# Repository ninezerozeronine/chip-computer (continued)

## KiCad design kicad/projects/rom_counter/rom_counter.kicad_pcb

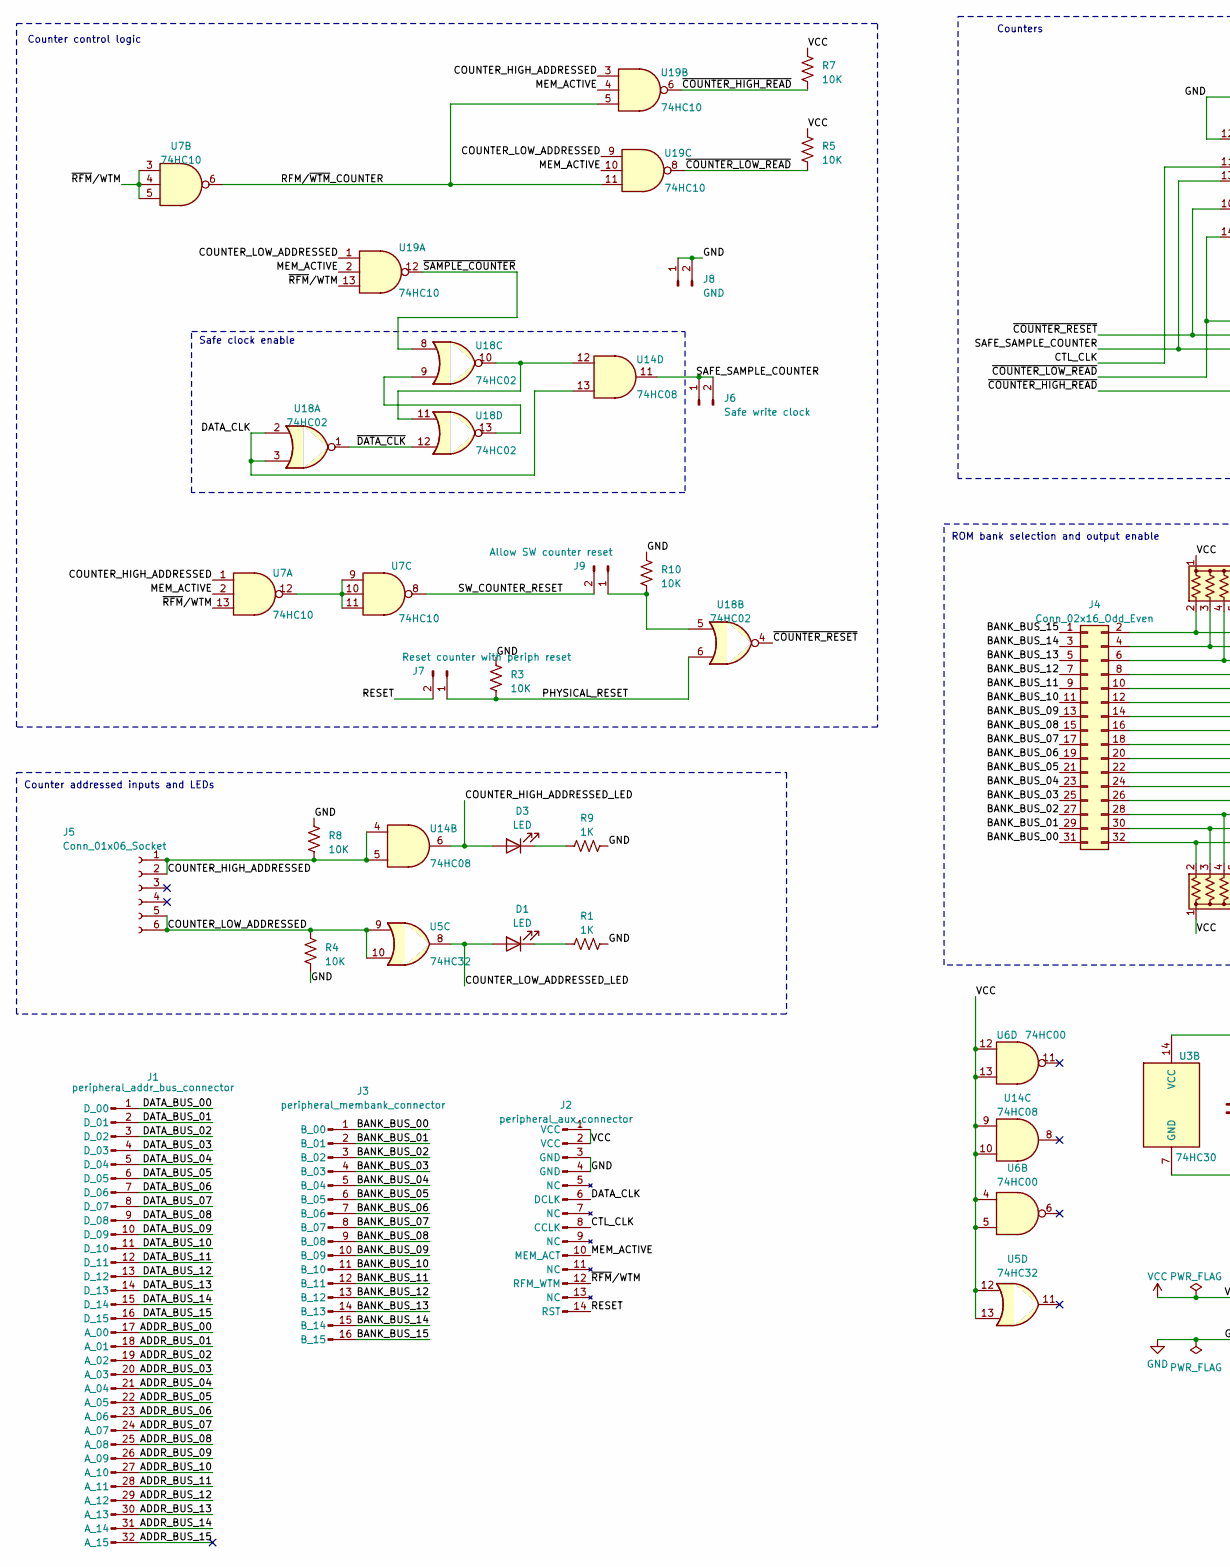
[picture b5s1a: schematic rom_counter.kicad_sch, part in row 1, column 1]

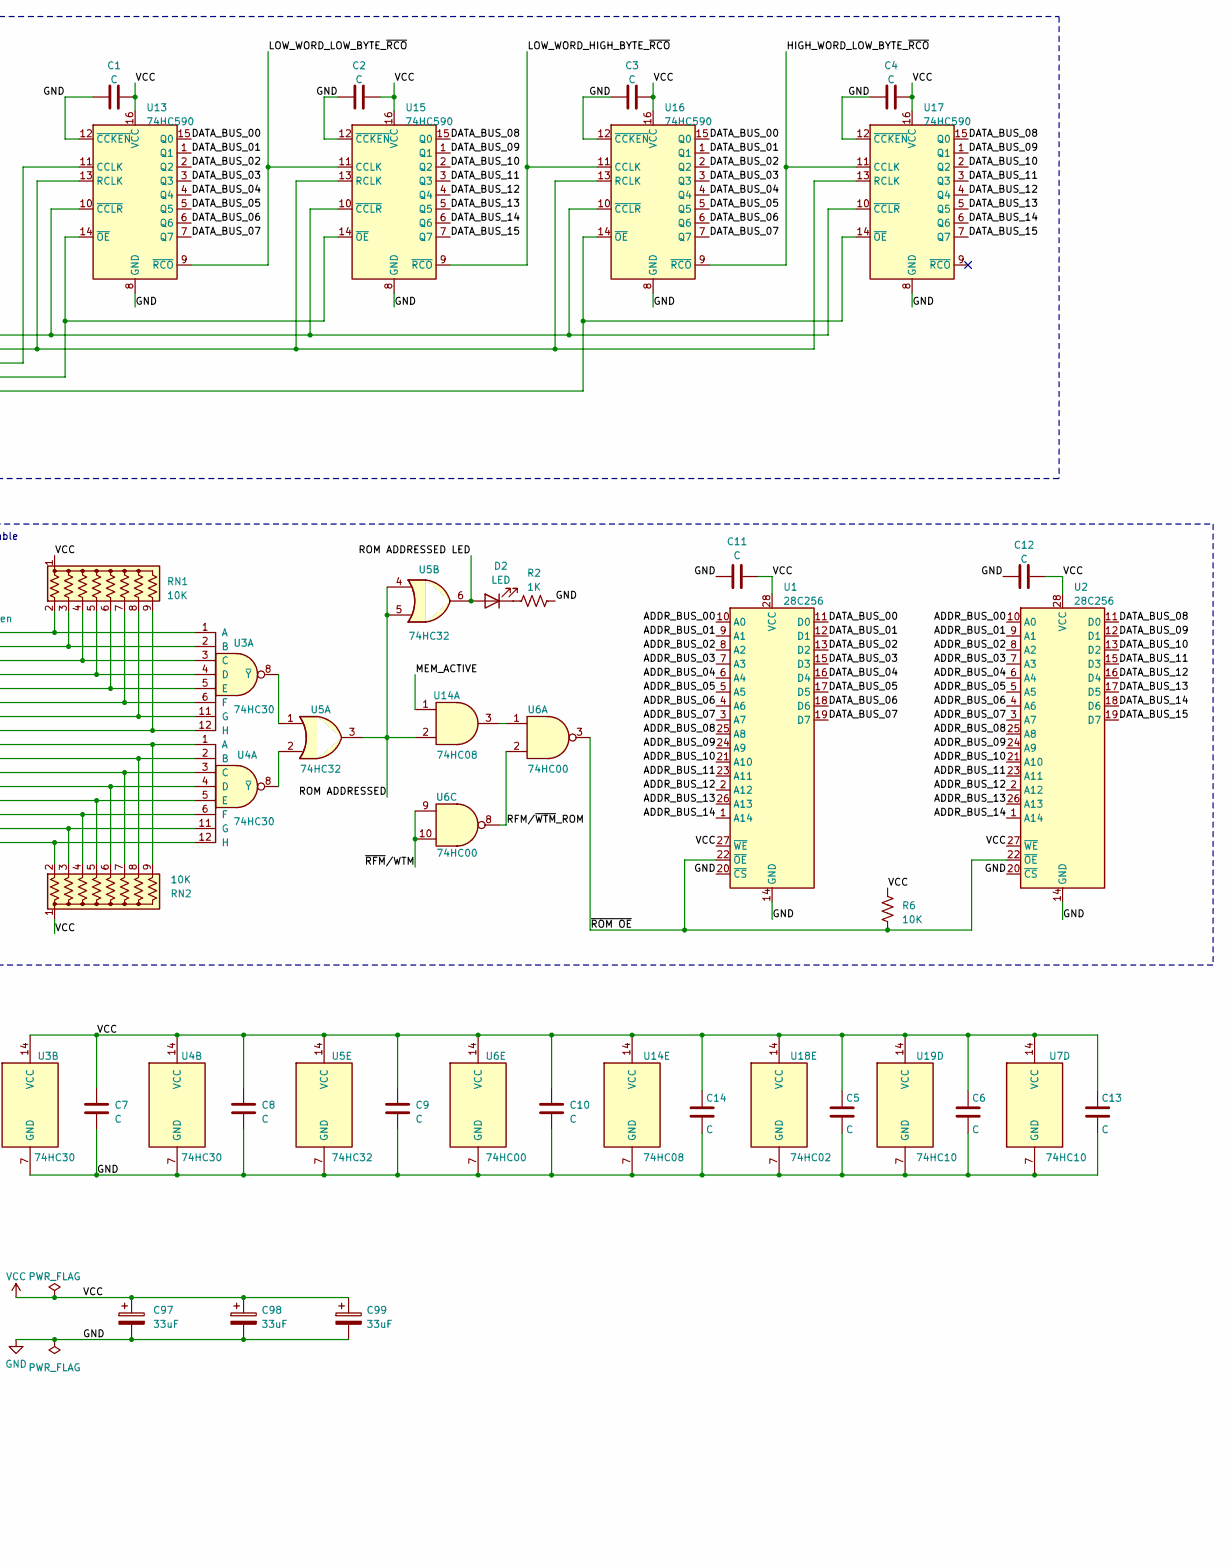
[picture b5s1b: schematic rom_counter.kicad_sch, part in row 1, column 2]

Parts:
C1, C2, C3, C4, C5, C6, C7, C8, C9, C10, C11, C12, C13, C14: C; C_Disc_D5.0mm_W2.5mm_P5.00mm
C97, C98, C99: 33uF; CP_Radial_D6.3mm_P2.50mm
D1, D2, D3: LED; LED_D5.0mm_Horizontal_O3.81mm_Z3.0mm
J1: peripheral_addr_bus_connector; peripheral-backplane-data-addr-anno
J2: peripheral_aux_connector; peripheral-backplane-aux
J3: peripheral_membank_connector; peripheral-backplane-membank
J4: Conn_02x16_Odd_Even; PinHeader_2x16_P2.54mm_Vertical
J5: Conn_01x06_Socket; PinSocket_1x06_P2.54mm_Horizontal
J6: Safe write clock; PinHeader_1x02_P2.54mm_Vertical
J7: Reset counter with periph reset; PinHeader_1x02_P2.54mm_Horizontal
J8: GND; PinHeader_1x02_P2.54mm_Vertical
J9: Allow SW counter reset; PinHeader_1x02_P2.54mm_Horizontal
R1, R2, R9: 1K; R_Axial_DIN0207_L6.3mm_D2.5mm_P10.16mm_Horizontal
R3, R4, R5, R6, R7, R8, R10: 10K; R_Axial_DIN0207_L6.3mm_D2.5mm_P10.16mm_Horizontal
RN1, RN2: 10K; R_Array_SIP9
U1, U2: 28C256; DIP-28_W15.24mm_Socket
U3, U4: 74HC30; DIP-14_W7.62mm_Socket
U5: 74HC32; DIP-14_W7.62mm_Socket
U6: 74HC00; DIP-14_W7.62mm_Socket
U7, U19: 74HC10; DIP-14_W7.62mm_Socket
U13, U15, U16, U17: 74HC590; DIP-16_W7.62mm_Socket
U14: 74HC08; DIP-14_W7.62mm_Socket
U18: 74HC02; DIP-14_W7.62mm_Socket

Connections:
/ADDR_BUS_00: J1.17 (A_00), U1.10 (A0), U2.10 (A0)
/ADDR_BUS_01: J1.18 (A_01), U1.9 (A1), U2.9 (A1)
/ADDR_BUS_02: J1.19 (A_02), U1.8 (A2), U2.8 (A2)
/ADDR_BUS_03: J1.20 (A_03), U1.7 (A3), U2.7 (A3)
/ADDR_BUS_04: J1.21 (A_04), U1.6 (A4), U2.6 (A4)
/ADDR_BUS_05: J1.22 (A_05), U1.5 (A5), U2.5 (A5)
/ADDR_BUS_06: J1.23 (A_06), U1.4 (A6), U2.4 (A6)
/ADDR_BUS_07: J1.24 (A_07), U1.3 (A7), U2.3 (A7)
/ADDR_BUS_08: J1.25 (A_08), U1.25 (A8), U2.25 (A8)
/ADDR_BUS_09: J1.26 (A_09), U1.24 (A9), U2.24 (A9)
/ADDR_BUS_10: J1.27 (A_10), U1.21 (A10), U2.21 (A10)
/ADDR_BUS_11: J1.28 (A_11), U1.23 (A11), U2.23 (A11)
/ADDR_BUS_12: J1.29 (A_12), U1.2 (A12), U2.2 (A12)
/ADDR_BUS_13: J1.30 (A_13), U1.26 (A13), U2.26 (A13)
/ADDR_BUS_14: J1.31 (A_14), U1.1 (A14), U2.1 (A14)
/ADDR_BUS_15: J1.32 (A_15)
/BANK_BUS_00: J3.1 (B_00), J4.31
/BANK_BUS_01: J3.2 (B_01), J4.29
/BANK_BUS_02: J3.3 (B_02), J4.27
/BANK_BUS_03: J3.4 (B_03), J4.25
/BANK_BUS_04: J3.5 (B_04), J4.23
/BANK_BUS_05: J3.6 (B_05), J4.21
/BANK_BUS_06: J3.7 (B_06), J4.19
/BANK_BUS_07: J3.8 (B_07), J4.17
/BANK_BUS_08: J3.9 (B_08), J4.15
/BANK_BUS_09: J3.10 (B_09), J4.13
/BANK_BUS_10: J3.11 (B_10), J4.11
/BANK_BUS_11: J3.12 (B_11), J4.9
/BANK_BUS_12: J3.13 (B_12), J4.7
/BANK_BUS_13: J3.14 (B_13), J4.5
/BANK_BUS_14: J3.15 (B_14), J4.3
/BANK_BUS_15: J3.16 (B_15), J4.1
/COUNTER_HIGH_ADDRESSED: J5.1, J5.2, R8.1, U7.1, U14.4, U14.5, U19.3
/COUNTER_HIGH_ADDRESSED_LED: D3.2 (A), U14.6
/COUNTER_LOW_ADDRESSED: J5.5, J5.6, R4.2, U5.9, U5.10, U19.1, U19.9
/COUNTER_LOW_ADDRESSED_LED: D1.2 (A), U5.8
/CTL_CLK: J2.8 (CCLK), U13.11 (CCLK)
/DATA_BUS_00: J1.1 (D_00), U1.11 (D0), U13.15 (Q0), U16.15 (Q0)
/DATA_BUS_01: J1.2 (D_01), U1.12 (D1), U13.1 (Q1), U16.1 (Q1)
/DATA_BUS_02: J1.3 (D_02), U1.13 (D2), U13.2 (Q2), U16.2 (Q2)
/DATA_BUS_03: J1.4 (D_03), U1.15 (D3), U13.3 (Q3), U16.3 (Q3)
/DATA_BUS_04: J1.5 (D_04), U1.16 (D4), U13.4 (Q4), U16.4 (Q4)
/DATA_BUS_05: J1.6 (D_05), U1.17 (D5), U13.5 (Q5), U16.5 (Q5)
/DATA_BUS_06: J1.7 (D_06), U1.18 (D6), U13.6 (Q6), U16.6 (Q6)
/DATA_BUS_07: J1.8 (D_07), U1.19 (D7), U13.7 (Q7), U16.7 (Q7)
/DATA_BUS_08: J1.9 (D_08), U2.11 (D0), U15.15 (Q0), U17.15 (Q0)
/DATA_BUS_09: J1.10 (D_09), U2.12 (D1), U15.1 (Q1), U17.1 (Q1)
/DATA_BUS_10: J1.11 (D_10), U2.13 (D2), U15.2 (Q2), U17.2 (Q2)
/DATA_BUS_11: J1.12 (D_11), U2.15 (D3), U15.3 (Q3), U17.3 (Q3)
/DATA_BUS_12: J1.13 (D_12), U2.16 (D4), U15.4 (Q4), U17.4 (Q4)
/DATA_BUS_13: J1.14 (D_13), U2.17 (D5), U15.5 (Q5), U17.5 (Q5)
/DATA_BUS_14: J1.15 (D_14), U2.18 (D6), U15.6 (Q6), U17.6 (Q6)
/DATA_BUS_15: J1.16 (D_15), U2.19 (D7), U15.7 (Q7), U17.7 (Q7)
/DATA_CLK: J2.6 (DCLK), U14.13, U18.2, U18.3
/HIGH_WORD_LOW_BYTE_~RCO: U16.9 (~RCO), U17.11 (CCLK)
/LOW_WORD_HIGH_BYTE_~RCO: U15.9 (~RCO), U16.11 (CCLK)
/LOW_WORD_LOW_BYTE_~RCO: U13.9 (~RCO), U15.11 (CCLK)
/MEM_ACTIVE: J2.10 (MEM_ACT), U7.2, U14.1, U19.2, U19.4, U19.10
/PHYSICAL_RESET: J7.1, R3.1, U18.6
/RESET: J2.14 (RST), J7.2
/RFM/~WTM_COUNTER: U7.6, U19.5, U19.11
/RFM/~WTM_ROM: U6.2, U6.8
/ROM ADDRESSED: U5.3, U5.4, U5.5, U14.2
/ROM ADDRESSED LED: D2.2 (A), U5.6
/SAFE_SAMPLE_COUNTER: J6.1, J6.2, U13.13 (RCLK), U14.11, U15.13 (RCLK), U16.13 (RCLK), U17.13 (RCLK)
/SW_COUNTER_RESET: J9.2, U7.8
/~COUNTER_HIGH_READ: R7.1, U16.14 (~OE), U17.14 (~OE), U19.6
/~COUNTER_LOW_READ: R5.1, U13.14 (~OE), U15.14 (~OE), U19.8
/~COUNTER_RESET: U13.10 (~CCLR), U15.10 (~CCLR), U16.10 (~CCLR), U17.10 (~CCLR), U18.4
/~DATA_CLK: U18.1, U18.12
/~RFM/WTM: J2.12 (RFM_WTM), U6.9, U6.10, U7.3, U7.4, U7.5, U7.13, U19.13
/~ROM OE: R6.2, U1.22 (~OE), U2.22 (~OE), U6.3
/~SAMPLE_COUNTER: U18.8, U19.12
GND: C1.1, C2.1, C3.1, C4.1, C5.1, C6.1, C7.1, C8.1, C9.1, C10.1, C11.2, C12.2, C13.1, C14.1, C97.2, C98.2, C99.2, J2.3 (GND), J2.4 (GND), J8.1, J8.2, R1.2, R2.2, R3.2, R4.1, R8.2, R9.2, R10.1, U1.14 (GND), U1.20 (~CS), U2.14 (GND), U2.20 (~CS), U3.7 (GND), U4.7 (GND), U5.7 (GND), U6.7 (GND), U7.7 (GND), U13.8 (GND), U13.12 (~CCKEN), U14.7 (GND), U15.8 (GND), U15.12 (~CCKEN), U16.8 (GND), U16.12 (~CCKEN), U17.8 (GND), U17.12 (~CCKEN), U18.7 (GND), U19.7 (GND)
unnamed: D1.1 (K), R1.1
unnamed: D2.1 (K), R2.1
unnamed: D3.1 (K), R9.1
unnamed: J4.2, RN1.2 (R1), U3.1 (A)
unnamed: J4.4, RN1.3 (R2), U3.2 (B)
unnamed: J4.6, RN1.4 (R3), U3.3 (C)
unnamed: J4.8, RN1.5 (R4), U3.4 (D)
unnamed: J4.10, RN1.6 (R5), U3.5 (E)
unnamed: J4.12, RN1.7 (R6), U3.6 (F)
unnamed: J4.14, RN1.8 (R7), U3.11 (G)
unnamed: J4.16, RN1.9 (R8), U3.12 (H)
unnamed: J4.18, RN2.9 (R8), U4.1 (A)
unnamed: J4.20, RN2.8 (R7), U4.2 (B)
unnamed: J4.22, RN2.7 (R6), U4.3 (C)
unnamed: J4.24, RN2.6 (R5), U4.4 (D)
unnamed: J4.26, RN2.5 (R4), U4.5 (E)
unnamed: J4.28, RN2.4 (R3), U4.6 (F)
unnamed: J4.30, RN2.3 (R2), U4.11 (G)
unnamed: J4.32, RN2.2 (R1), U4.12 (H)
unnamed: J9.1, R10.2, U18.5
unnamed: U3.8 (~Y), U5.1
unnamed: U4.8 (~Y), U5.2
unnamed: U7.9, U7.10, U7.11, U7.12
unnamed: U6.1, U14.3
unnamed: U14.12, U18.10, U18.11
unnamed: U18.9, U18.13
VCC: C1.2, C2.2, C3.2, C4.2, C5.2, C6.2, C7.2, C8.2, C9.2, C10.2, C11.1, C12.1, C13.2, C14.2, C97.1, C98.1, C99.1, J2.1 (VCC), J2.2 (VCC), R5.2, R6.1, R7.2, RN1.1 (common), RN2.1 (common), U1.27 (~WE), U1.28 (VCC), U2.27 (~WE), U2.28 (VCC), U3.14 (VCC), U4.14 (VCC), U5.12, U5.13, U5.14 (VCC), U6.4, U6.5, U6.12, U6.13, U6.14 (VCC), U7.14 (VCC), U13.16 (VCC), U14.9, U14.10, U14.14 (VCC), U15.16 (VCC), U16.16 (VCC), U17.16 (VCC), U18.14 (VCC), U19.14 (VCC)

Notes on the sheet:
Safe clock enable
ROM bank selection and output enable
Counters
Counter addressed inputs and LEDs
Counter control logic

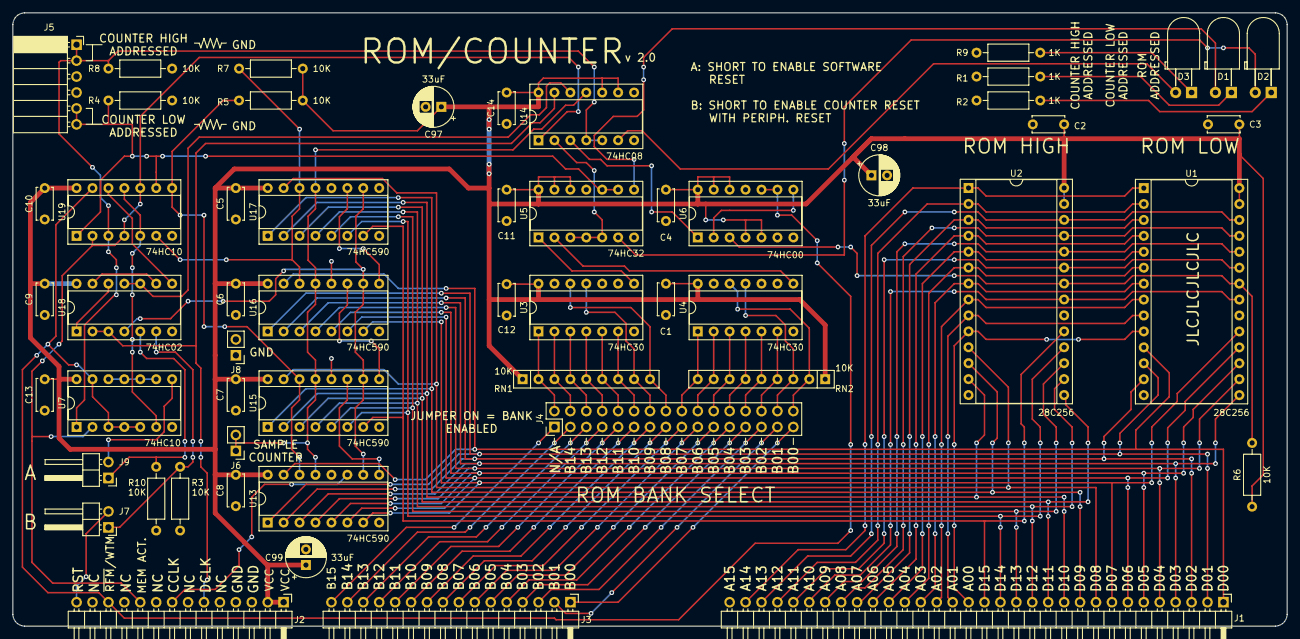
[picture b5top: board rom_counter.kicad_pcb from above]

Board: 2 copper layers, 203.2 x 97.8 mm, 55 parts (0 on the bottom side), 100 nets.

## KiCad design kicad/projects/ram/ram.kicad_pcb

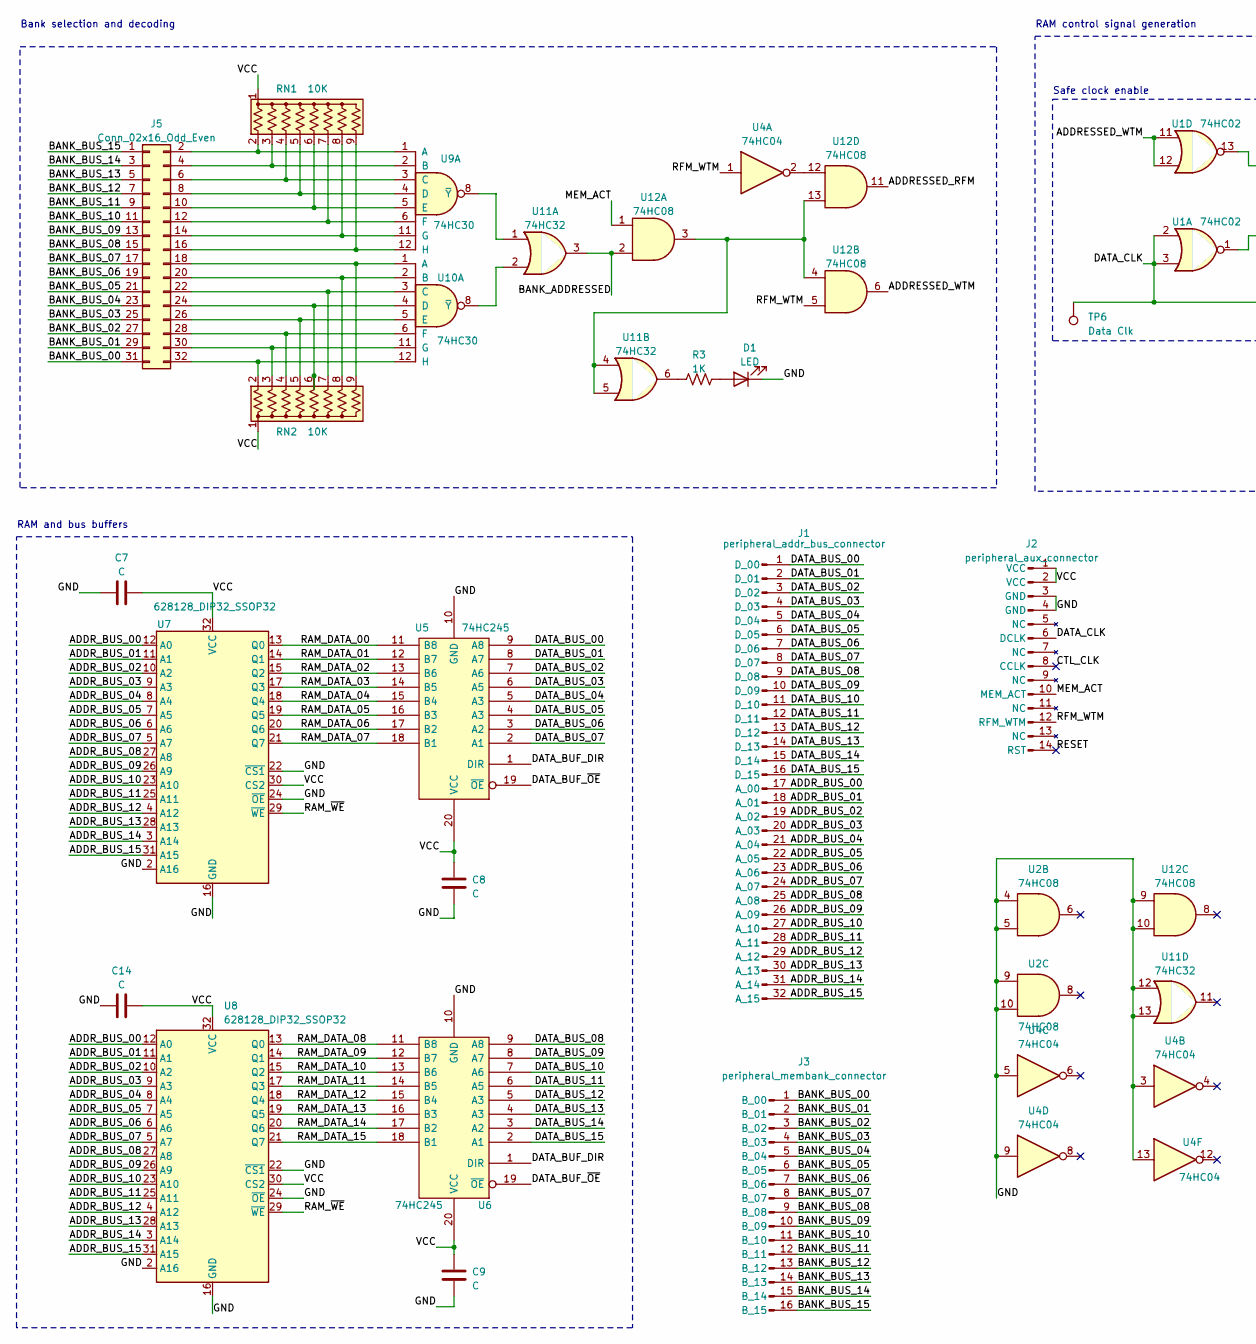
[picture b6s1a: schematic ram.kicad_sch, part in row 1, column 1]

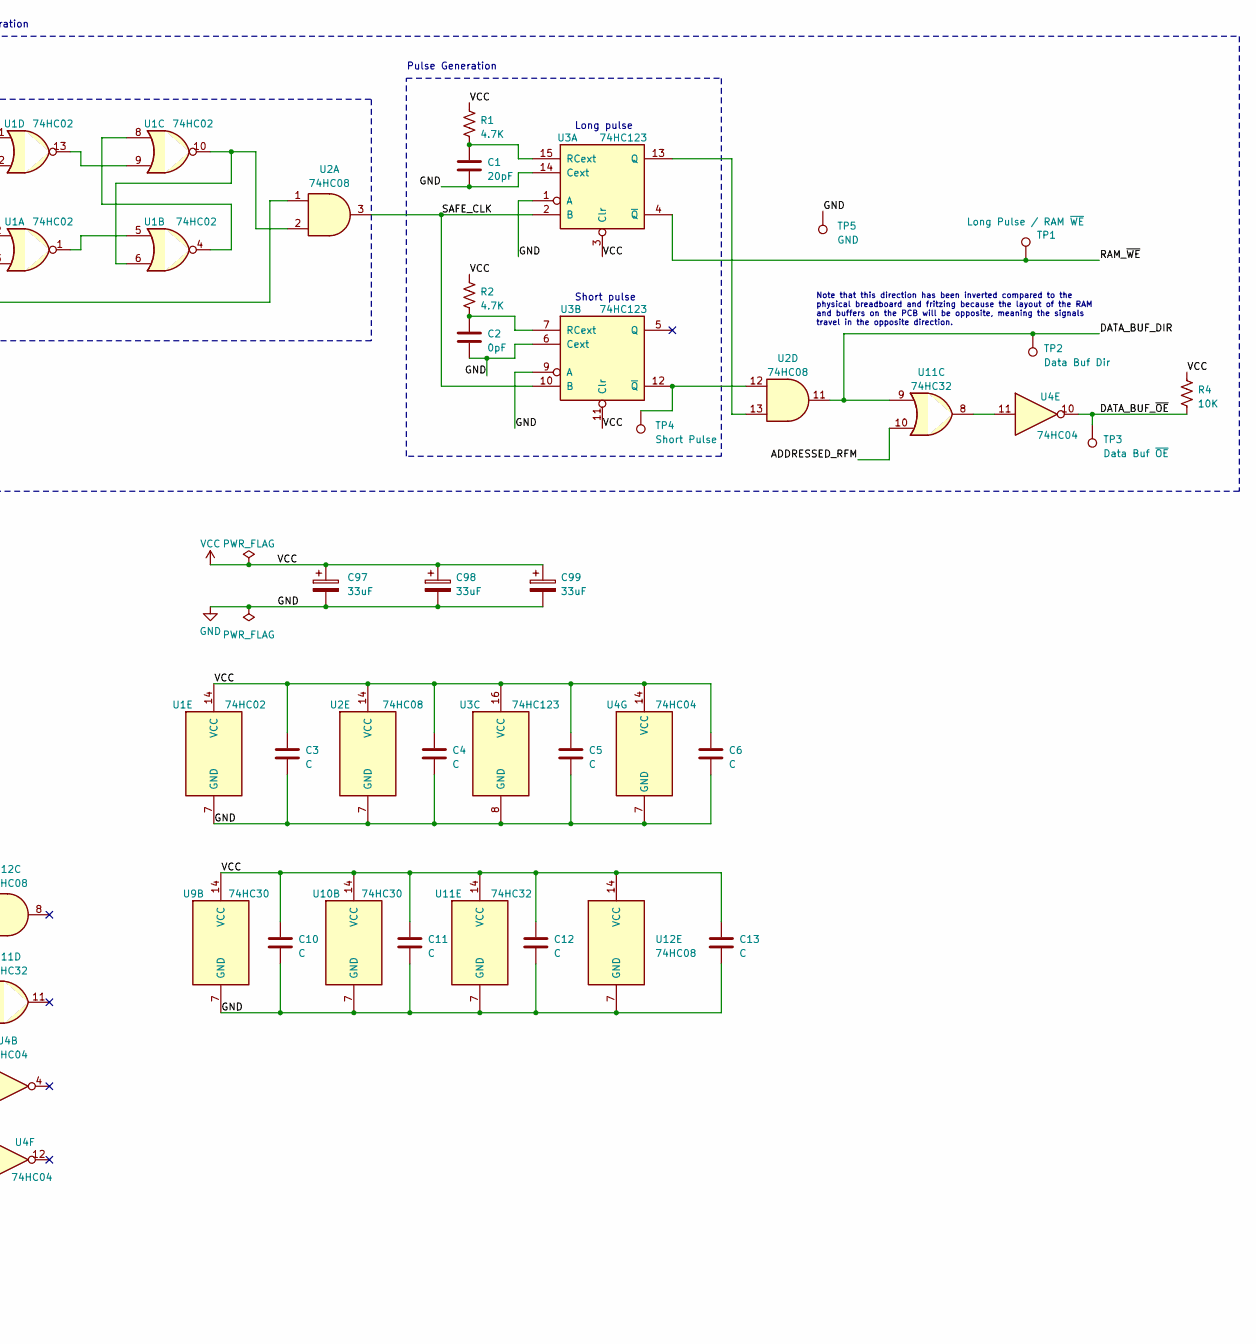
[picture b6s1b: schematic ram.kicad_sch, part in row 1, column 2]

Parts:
C1: 20pF; C_Disc_D5.0mm_W2.5mm_P5.00mm
C2: 0pF; C_Disc_D5.0mm_W2.5mm_P5.00mm
C3, C4, C5, C6, C7, C8, C9, C10, C11, C12, C13, C14: C; C_Disc_D5.0mm_W2.5mm_P5.00mm
C97, C98, C99: 33uF; CP_Radial_D6.3mm_P2.50mm
D1: LED; LED_D5.0mm_Horizontal_O3.81mm_Z3.0mm
J1: peripheral_addr_bus_connector; peripheral-backplane-data-addr-anno
J2: peripheral_aux_connector; peripheral-backplane-aux
J3: peripheral_membank_connector; peripheral-backplane-membank
J5: Conn_02x16_Odd_Even; PinHeader_2x16_P2.54mm_Vertical
R1, R2: 4.7K; R_Axial_DIN0207_L6.3mm_D2.5mm_P10.16mm_Horizontal
R3: 1K; R_Axial_DIN0207_L6.3mm_D2.5mm_P10.16mm_Horizontal
R4: 10K; R_Axial_DIN0207_L6.3mm_D2.5mm_P10.16mm_Horizontal
RN1, RN2: 10K; R_Array_SIP9
TP1: Long Pulse / RAM ~{WE}; Pin_D1.0mm_L10.0mm
TP2: Data Buf Dir; Pin_D1.0mm_L10.0mm
TP3: Data Buf ~{OE}; Pin_D1.0mm_L10.0mm
TP4: Short Pulse; Pin_D1.0mm_L10.0mm
TP5: GND; Pin_D1.0mm_L10.0mm
TP6: Data Clk; Pin_D1.0mm_L10.0mm
U1: 74HC02; DIP-14_W7.62mm_Socket
U2, U12: 74HC08; DIP-14_W7.62mm_Socket
U3: 74HC123; DIP-16_W7.62mm_Socket
U4: 74HC04; DIP-14_W7.62mm_Socket
U5, U6: 74HC245; DIP-20_W7.62mm_Socket
U7, U8: 628128_DIP32_SSOP32; DIP-32_W15.24mm_Socket
U9, U10: 74HC30; DIP-14_W7.62mm_Socket
U11: 74HC32; DIP-14_W7.62mm_Socket

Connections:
/ADDRESSED_RFM: U11.10, U12.11
/ADDRESSED_WTM: U1.11, U1.12, U12.6
/ADDR_BUS_00: J1.17 (A_00), U7.12 (A0), U8.12 (A0)
/ADDR_BUS_01: J1.18 (A_01), U7.11 (A1), U8.11 (A1)
/ADDR_BUS_02: J1.19 (A_02), U7.10 (A2), U8.10 (A2)
/ADDR_BUS_03: J1.20 (A_03), U7.9 (A3), U8.9 (A3)
/ADDR_BUS_04: J1.21 (A_04), U7.8 (A4), U8.8 (A4)
/ADDR_BUS_05: J1.22 (A_05), U7.7 (A5), U8.7 (A5)
/ADDR_BUS_06: J1.23 (A_06), U7.6 (A6), U8.6 (A6)
/ADDR_BUS_07: J1.24 (A_07), U7.5 (A7), U8.5 (A7)
/ADDR_BUS_08: J1.25 (A_08), U7.27 (A8), U8.27 (A8)
/ADDR_BUS_09: J1.26 (A_09), U7.26 (A9), U8.26 (A9)
/ADDR_BUS_10: J1.27 (A_10), U7.23 (A10), U8.23 (A10)
/ADDR_BUS_11: J1.28 (A_11), U7.25 (A11), U8.25 (A11)
/ADDR_BUS_12: J1.29 (A_12), U7.4 (A12), U8.4 (A12)
/ADDR_BUS_13: J1.30 (A_13), U7.28 (A13), U8.28 (A13)
/ADDR_BUS_14: J1.31 (A_14), U7.3 (A14), U8.3 (A14)
/ADDR_BUS_15: J1.32 (A_15), U7.31 (A15), U8.31 (A15)
/BANK_ADDRESSED: U11.3, U12.2
/BANK_BUS_00: J3.1 (B_00), J5.31
/BANK_BUS_01: J3.2 (B_01), J5.29
/BANK_BUS_02: J3.3 (B_02), J5.27
/BANK_BUS_03: J3.4 (B_03), J5.25
/BANK_BUS_04: J3.5 (B_04), J5.23
/BANK_BUS_05: J3.6 (B_05), J5.21
/BANK_BUS_06: J3.7 (B_06), J5.19
/BANK_BUS_07: J3.8 (B_07), J5.17
/BANK_BUS_08: J3.9 (B_08), J5.15
/BANK_BUS_09: J3.10 (B_09), J5.13
/BANK_BUS_10: J3.11 (B_10), J5.11
/BANK_BUS_11: J3.12 (B_11), J5.9
/BANK_BUS_12: J3.13 (B_12), J5.7
/BANK_BUS_13: J3.14 (B_13), J5.5
/BANK_BUS_14: J3.15 (B_14), J5.3
/BANK_BUS_15: J3.16 (B_15), J5.1
/CTL_CLK: J2.8 (CCLK)
/DATA_BUF_DIR: TP2.1, U2.11, U5.1 (DIR), U6.1 (DIR), U11.9
/DATA_BUF_~OE: R4.2, TP3.1, U4.10, U5.19 (~OE), U6.19 (~OE)
/DATA_BUS_00: J1.1 (D_00), U5.9 (A8)
/DATA_BUS_01: J1.2 (D_01), U5.8 (A7)
/DATA_BUS_02: J1.3 (D_02), U5.7 (A6)
/DATA_BUS_03: J1.4 (D_03), U5.6 (A5)
/DATA_BUS_04: J1.5 (D_04), U5.5 (A3)
/DATA_BUS_05: J1.6 (D_05), U5.4 (A3)
/DATA_BUS_06: J1.7 (D_06), U5.3 (A2)
/DATA_BUS_07: J1.8 (D_07), U5.2 (A1)
/DATA_BUS_08: J1.9 (D_08), U6.9 (A8)
/DATA_BUS_09: J1.10 (D_09), U6.8 (A7)
/DATA_BUS_10: J1.11 (D_10), U6.7 (A6)
/DATA_BUS_11: J1.12 (D_11), U6.6 (A5)
/DATA_BUS_12: J1.13 (D_12), U6.5 (A3)
/DATA_BUS_13: J1.14 (D_13), U6.4 (A3)
/DATA_BUS_14: J1.15 (D_14), U6.3 (A2)
/DATA_BUS_15: J1.16 (D_15), U6.2 (A1)
/DATA_CLK: J2.6 (DCLK), TP6.1, U1.2, U1.3, U2.1
/MEM_ACT: J2.10 (MEM_ACT), U12.1
/RAM_DATA_00: U5.11 (B8), U7.13 (Q0)
/RAM_DATA_01: U5.12 (B7), U7.14 (Q1)
/RAM_DATA_02: U5.13 (B6), U7.15 (Q2)
/RAM_DATA_03: U5.14 (B5), U7.17 (Q3)
/RAM_DATA_04: U5.15 (B4), U7.18 (Q4)
/RAM_DATA_05: U5.16 (B3), U7.19 (Q5)
/RAM_DATA_06: U5.17 (B2), U7.20 (Q6)
/RAM_DATA_07: U5.18 (B1), U7.21 (Q7)
/RAM_DATA_08: U6.11 (B8), U8.13 (Q0)
/RAM_DATA_09: U6.12 (B7), U8.14 (Q1)
/RAM_DATA_10: U6.13 (B6), U8.15 (Q2)
/RAM_DATA_11: U6.14 (B5), U8.17 (Q3)
/RAM_DATA_12: U6.15 (B4), U8.18 (Q4)
/RAM_DATA_13: U6.16 (B3), U8.19 (Q5)
/RAM_DATA_14: U6.17 (B2), U8.20 (Q6)
/RAM_DATA_15: U6.18 (B1), U8.21 (Q7)
/RAM_~WE: TP1.1, U3.4 (~Q), U7.29 (~WE), U8.29 (~WE)
/RESET: J2.14 (RST)
/RFM_WTM: J2.12 (RFM_WTM), U4.1, U12.5
/SAFE_CLK: U2.3, U3.2 (B), U3.10 (B)
GND: C1.1, C2.1, C3.2, C4.2, C5.2, C6.2, C7.1, C8.1, C9.1, C10.2, C11.2, C12.2, C13.2, C14.1, C97.2, C98.2, C99.2, D1.1 (K), J2.3 (GND), J2.4 (GND), TP5.1, U1.7 (GND), U2.4, U2.5, U2.7 (GND), U2.9, U2.10, U3.1 (A), U3.6 (Cext), U3.8 (GND), U3.9 (A), U3.14 (Cext), U4.3, U4.5, U4.7 (GND), U4.9, U4.13, U5.10 (GND), U6.10 (GND), U7.2 (A16), U7.16 (GND), U7.22 (~CS1), U7.24 (~OE), U8.2 (A16), U8.16 (GND), U8.22 (~CS1), U8.24 (~OE), U9.7 (GND), U10.7 (GND), U11.7 (GND), U11.12, U11.13, U12.7 (GND), U12.9, U12.10
unnamed: D1.2 (A), R3.1
unnamed: J5.2, RN1.2 (R1), U9.1 (A)
unnamed: J5.4, RN1.3 (R2), U9.2 (B)
unnamed: J5.6, RN1.4 (R3), U9.3 (C)
unnamed: J5.8, RN1.5 (R4), U9.4 (D)
unnamed: J5.10, RN1.6 (R5), U9.5 (E)
unnamed: J5.12, RN1.7 (R6), U9.6 (F)
unnamed: J5.14, RN1.8 (R7), U9.11 (G)
unnamed: J5.16, RN1.9 (R8), U9.12 (H)
unnamed: J5.18, RN2.9 (R8), U10.1 (A)
unnamed: J5.20, RN2.8 (R7), U10.2 (B)
unnamed: J5.22, RN2.7 (R6), U10.3 (C)
unnamed: J5.24, RN2.6 (R5), U10.4 (D)
unnamed: J5.26, RN2.5 (R4), U10.5 (E)
unnamed: J5.28, RN2.4 (R3), U10.6 (F)
unnamed: J5.30, RN2.3 (R2), U10.11 (G)
unnamed: J5.32, RN2.2 (R1), U10.12 (H)
unnamed: R3.2, U11.6
unnamed: U1.1, U1.5
unnamed: U1.4, U1.8
unnamed: U1.6, U1.10, U2.2
unnamed: U1.9, U1.13
unnamed: U2.13, U3.13 (Q)
unnamed: C1.2, R1.2, U3.15 (RCext)
unnamed: C2.2, R2.2, U3.7 (RCext)
unnamed: TP4.1, U2.12, U3.12 (~Q)
unnamed: U9.8 (~Y), U11.1
unnamed: U10.8 (~Y), U11.2
unnamed: U11.4, U11.5, U12.3, U12.4, U12.13
unnamed: U4.11, U11.8
unnamed: U4.2, U12.12
VCC: C3.1, C4.1, C5.1, C6.1, C7.2, C8.2, C9.2, C10.1, C11.1, C12.1, C13.1, C14.2, C97.1, C98.1, C99.1, J2.1 (VCC), J2.2 (VCC), R1.1, R2.1, R4.1, RN1.1 (common), RN2.1 (common), U1.14 (VCC), U2.14 (VCC), U3.3 (Clr), U3.11 (Clr), U3.16 (VCC), U4.14 (VCC), U5.20 (VCC), U6.20 (VCC), U7.30 (CS2), U7.32 (VCC), U8.30 (CS2), U8.32 (VCC), U9.14 (VCC), U10.14 (VCC), U11.14 (VCC), U12.14 (VCC)

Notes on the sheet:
Note that this direction has been inverted compared to the physical breadboard and fritzing because the layout of the RAM and buffers on the PCB will be opposite, meaning the signals travel in the opposite direction.
RAM control signal generation
Safe clock enable
Short pulse
Pulse Generation
Bank selection and decoding
Long pulse
RAM and bus buffers

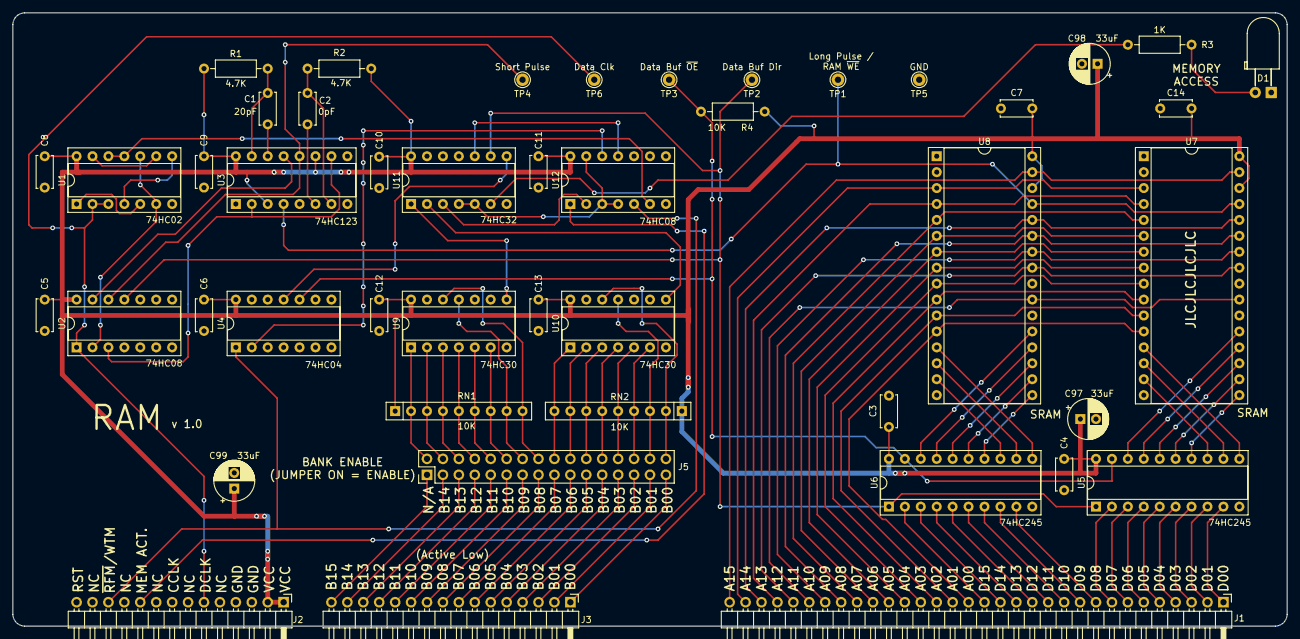
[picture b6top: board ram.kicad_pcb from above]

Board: 2 copper layers, 203.2 x 97.8 mm, 46 parts (0 on the bottom side), 107 nets.
